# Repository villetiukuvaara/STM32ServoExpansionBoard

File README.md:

# STM32ServoExpansionBoard
An STM32 Nucleo expansion board that provides 3 A of power at 5 V, voltage level conversion, and a Wii Nunchuck connector. Suitable for controlling a robotic arm, such as the EEZYbotARM MK2.

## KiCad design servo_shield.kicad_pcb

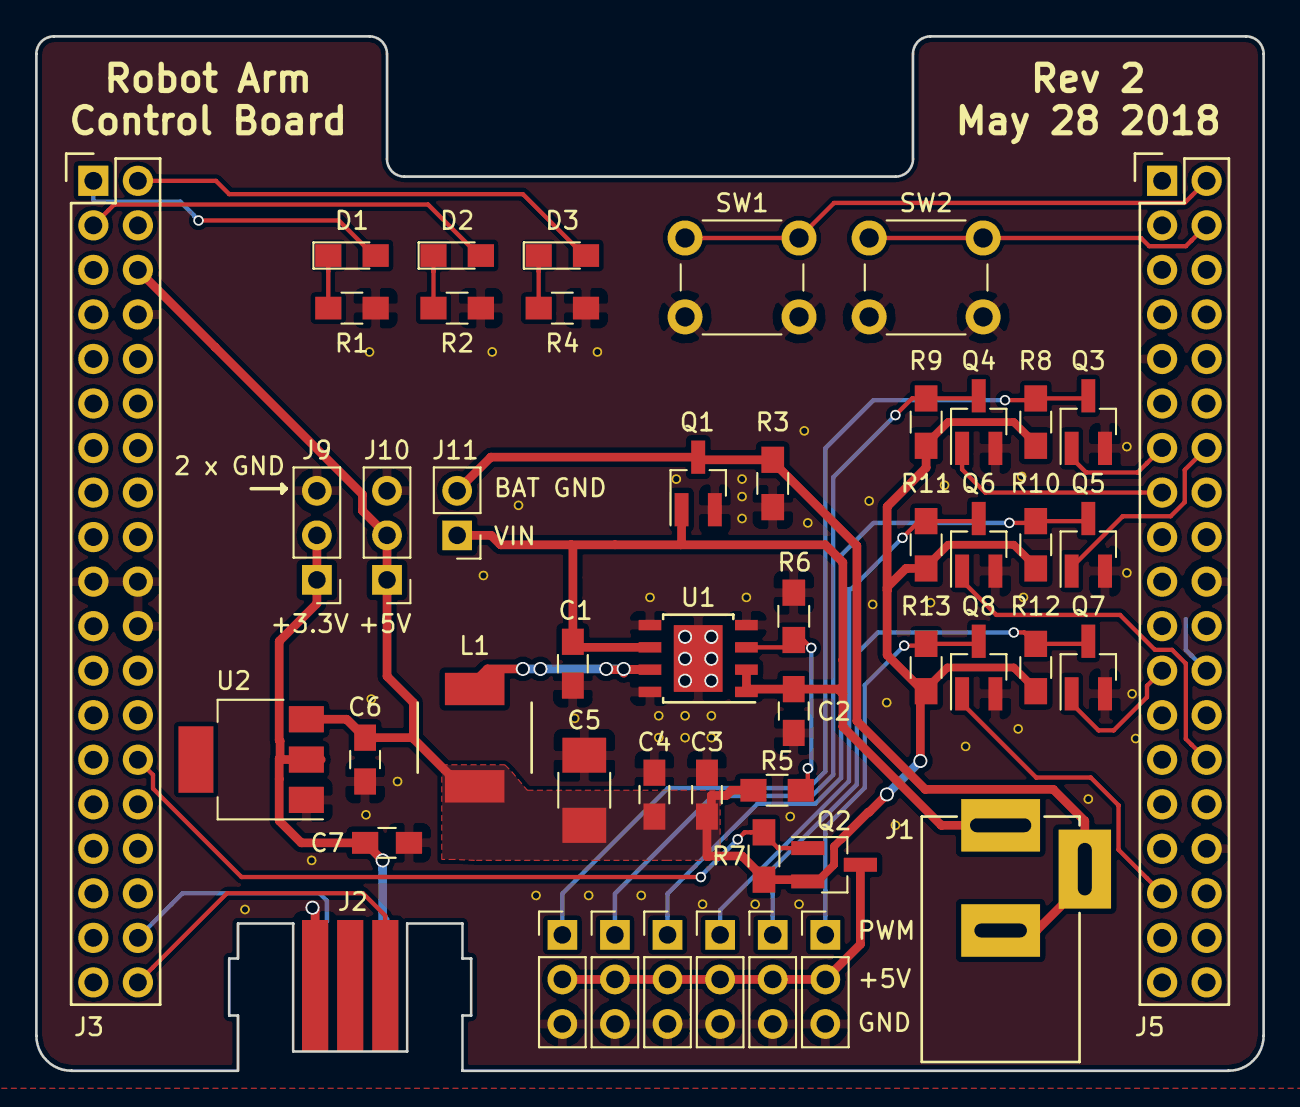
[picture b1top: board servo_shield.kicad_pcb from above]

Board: 2 copper layers, 70.0 x 59.0 mm, 49 parts (0 on the bottom side), 31 nets.

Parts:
C1, C7: 10u; C_0805_HandSoldering
C2, C6: 100n; C_0805_HandSoldering
C3: 22u; C_0805_HandSoldering
C4: DNI; C_0805_HandSoldering
C5: DNI; C_1210_HandSoldering
D1, D2, D3: LED; LED_0805_HandSoldering
J1: BARREL_JACK; DC-5020
J2: NUNCHUCK_CONN; NUNCHUCK_CONNECTOR
J3, J5: CONN_02X19; Pin_Header_Straight_2x19
J6, J7, J8, J9, J10, J12, J13, J14: CONN_01X03; Pin_Header_Straight_1x03_Pitch2.54mm
J11: CONN_01X02; Pin_Header_Straight_1x02_Pitch2.54mm
L1: 4.7u; TDK_SPM6530
Q1: Si2312BDS; SOT-23_Handsoldering
Q2: SI2323DS; SOT-23_Handsoldering
Q3, Q4, Q5, Q6, Q7, Q8: SI2304DDS; SOT-23_Handsoldering
R1, R2, R4: 220; R_0805_HandSoldering
R3: DNI; R_0805_HandSoldering
R5: 105k; R_0805_HandSoldering
R6: 20k; R_0805_HandSoldering
R7: 10k; R_0805_HandSoldering
R8, R9, R10, R11, R12, R13: 1k; R_0805_HandSoldering
SW1, SW2: SW_Push; SW_PUSH_6mm
U1: ST1S10; ST_PowerSO-8
U2: LD1117S33CTR; SOT-223

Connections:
+3V3: C7.1, J2.1, J9.1, J9.2, U2.2
+5V: C3.1, C4.1, C5.1, C6.1, J3.6, J10.1, J10.2, L1.1, Q2.2, R5.2, R7.2, R8.2, R9.2, R10.2, R11.2, R12.2, R13.2, U2.3
/BAT_GND: J1.2, J1.3, J11.2, Q1.3, R3.1
/I2C_SCL: J2.2, J3.38
/I2C_SDA: J2.5, J3.36
/LED1: D1.2, J3.1
/LED2: D2.2, J3.3
/LED3: D3.2, J3.2
/PA_6: J5.13, Q3.1
/PA_7: J5.15, Q4.1
/PA_8: J5.23, Q7.1
/PA_10: J5.33, Q8.1
/PA_11: J5.14, Q5.1
/PB_14: J5.28, Q6.1
/POW_EN: J3.28, Q2.1, R7.1
/SERVO_5V: J6.2, J7.2, J8.2, J12.2, J13.2, J14.2, Q2.3
/SWITCH1: J5.2, SW1.1
/SWITCH2: J5.4, SW2.1
/VIN: C1.1, C2.1, J1.1, J11.1, Q1.1, U1.1, U1.2, U1.6
GND: C1.2, C2.2, C3.2, C4.2, C5.2, C6.2, C7.2, J2.6, J3.8, J3.19, J3.20, J3.22, J5.9, J5.20, J5.32, J6.3, J7.3, J8.3, J9.3, J10.3, J12.3, J13.3, J14.3, Q1.2, Q3.2, Q4.2, Q5.2, Q6.2, Q7.2, Q8.2, R1.1, R2.1, R3.2, R4.2, R6.1, SW1.2, SW2.2, U1.4, U1.5, U1.8, U1.9, U2.1
unnamed: D1.1, R1.2
unnamed: D2.1, R2.2
unnamed: D3.1, R4.1
unnamed: J6.1, Q3.3, R8.1
unnamed: J7.1, Q4.3, R9.1
unnamed: J8.1, Q5.3, R10.1
unnamed: J12.1, Q6.3, R11.1
unnamed: J13.1, Q7.3, R12.1
unnamed: J14.1, Q8.3, R13.1
unnamed: L1.2, U1.7
unnamed: R5.1, R6.2, U1.3

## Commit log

2018-03-31 Added nunchuck connector; schematic pretty much done
2018-05-05 Rev 1 sent to fab
2018-05-05 Create README.md
    Added README
2018-05-05 Added PCB dimensions
2018-05-29 Revision 2
